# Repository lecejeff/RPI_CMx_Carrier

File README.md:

## SPONSOR

This project is proudly sponsored by [NextPCB](https://www.nextpcb.com). They have provided, free of charge, 2x assembled PCBA.

If you’re planning to build your own PCB, [NextPCB](https://www.nextpcb.com) offers reliable PCB fabrication and assembly services with fast turnaround times and competitive pricing, making it easier to bring your electronics projects from idea to reality.

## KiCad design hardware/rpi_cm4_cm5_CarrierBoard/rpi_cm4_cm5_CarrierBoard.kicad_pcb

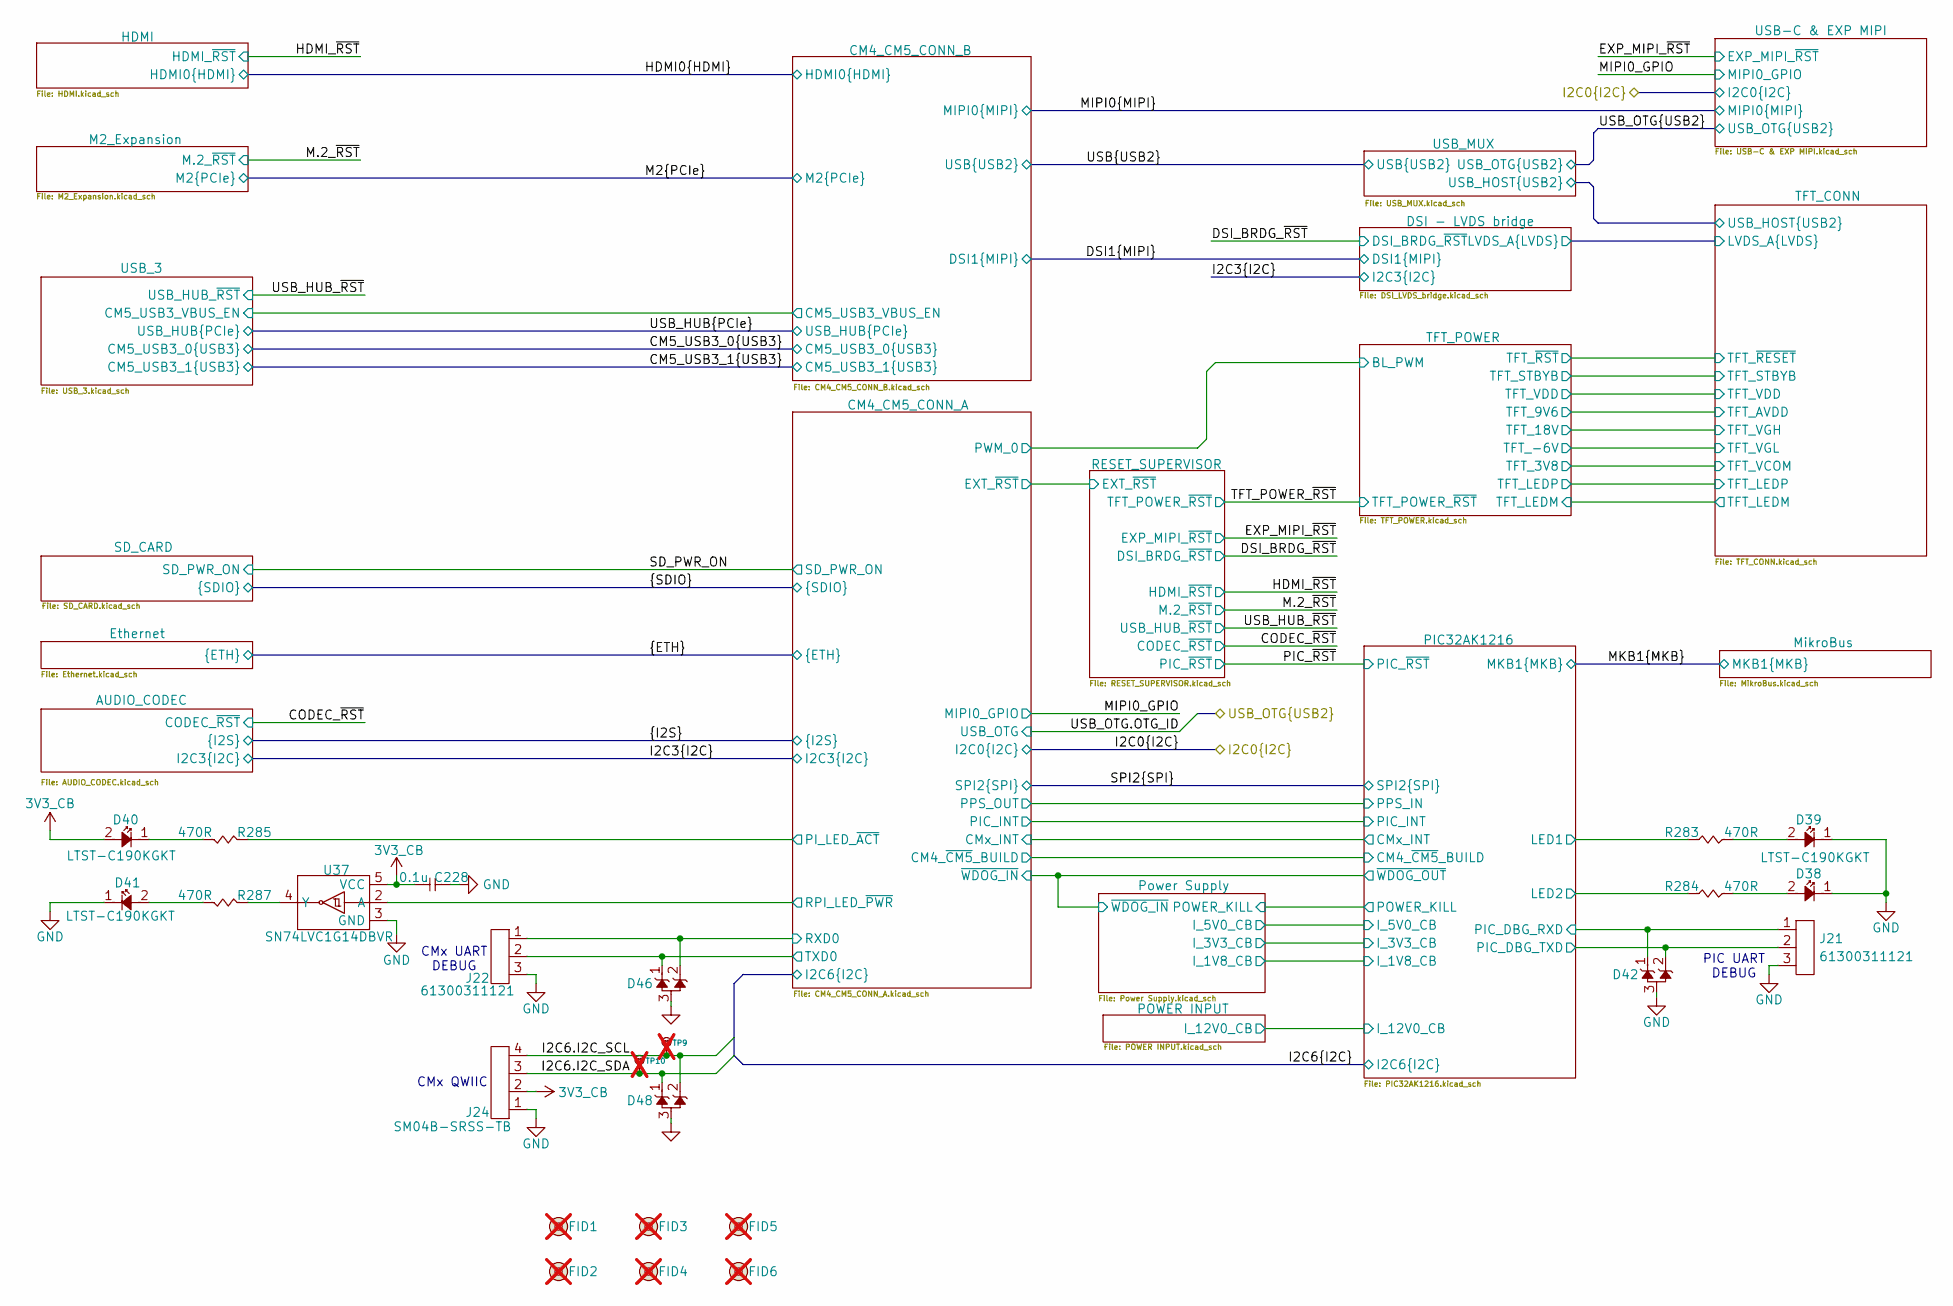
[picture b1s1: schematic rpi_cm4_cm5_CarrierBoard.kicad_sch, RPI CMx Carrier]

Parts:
C228: 0.1u; CAP_NONPOL_0402; Tolerance ±10%; Voltage Rating 50V; Manufacturer Part Number GRM155R71H104KE14D
D38, D39, D40, D41: LTST-C190KGKT; LED_0603; Tolerance NA; Manufacturer Part Number LTST-C190KGKT
D42, D46, D48: D1213A-02SOL-7; SOT-23-3; Manufacturer Part Number D1213A-02SOL-7
FID1, FID2, FID3, FID4, FID5, FID6: FIDUCIAL; not fitted
J21, J22: 61300311121; HEADER_3P_2_54MM; Current Rating 3A; Voltage Rating 250V; Manufacturer Part Number 61300311121
J24: SM04B-SRSS-TB; Current Rating 1A; Voltage Rating 50V; Manufacturer Part Number SM04B-SRSS-TB
R283, R284, R285, R287: 470R; RES_0402; Tolerance 1%; Manufacturer Part Number RC0402FR-07470RL
TP9, TP10: 28 mils; SMT_TP_28_MILS; Manufacturer Part Number NA; not fitted
U37: SN74LVC1G14DBVR; SOT-23-5; Supply Voltage 1.65V ~ 5.5V; Manufacturer Part Number SN74LVC1G14DBVR

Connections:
3V3_CB: C228.2, D40.2 (A), J24.2, U37.5 (VCC); also elsewhere on the board
/CM4_CM5_CONN_A/PI_LED_~ACT: R285.1; also elsewhere on the board
/CM4_CM5_CONN_A/RPI_LED_~PWR: U37.2 (A); also elsewhere on the board
/CM4_CM5_CONN_A/RXD0: D46.2 (A), J22.1; also elsewhere on the board
/CM4_CM5_CONN_A/TXD0: D46.1, J22.2; also elsewhere on the board
/I2C6.I2C_SCL: D48.2 (A), J24.4, TP9.1; also elsewhere on the board
/I2C6.I2C_SDA: D48.1, J24.3, TP10.1; also elsewhere on the board
/PIC32AK1216/LED1: R283.1; also elsewhere on the board
/PIC32AK1216/LED2: R284.1; also elsewhere on the board
/PIC32AK1216/PIC_DBG_RXD: D42.1, J21.1; also elsewhere on the board
/PIC32AK1216/PIC_DBG_TXD: D42.2 (A), J21.2; also elsewhere on the board
GND: C228.1, D38.1 (K), D39.1 (K), D41.1 (K), D42.3 (GND), D46.3 (GND), D48.3 (GND), J21.3, J22.3, J24.1, U37.3 (GND); also elsewhere on the board
unnamed: D38.2 (A), R284.2
unnamed: D39.2 (A), R283.2
unnamed: D40.1 (K), R285.2
unnamed: D41.2 (A), R287.2
unnamed: R287.1, U37.4 (Y)

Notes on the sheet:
CMx QWIIC
PIC UART DEBUG
CMx UART DEBUG

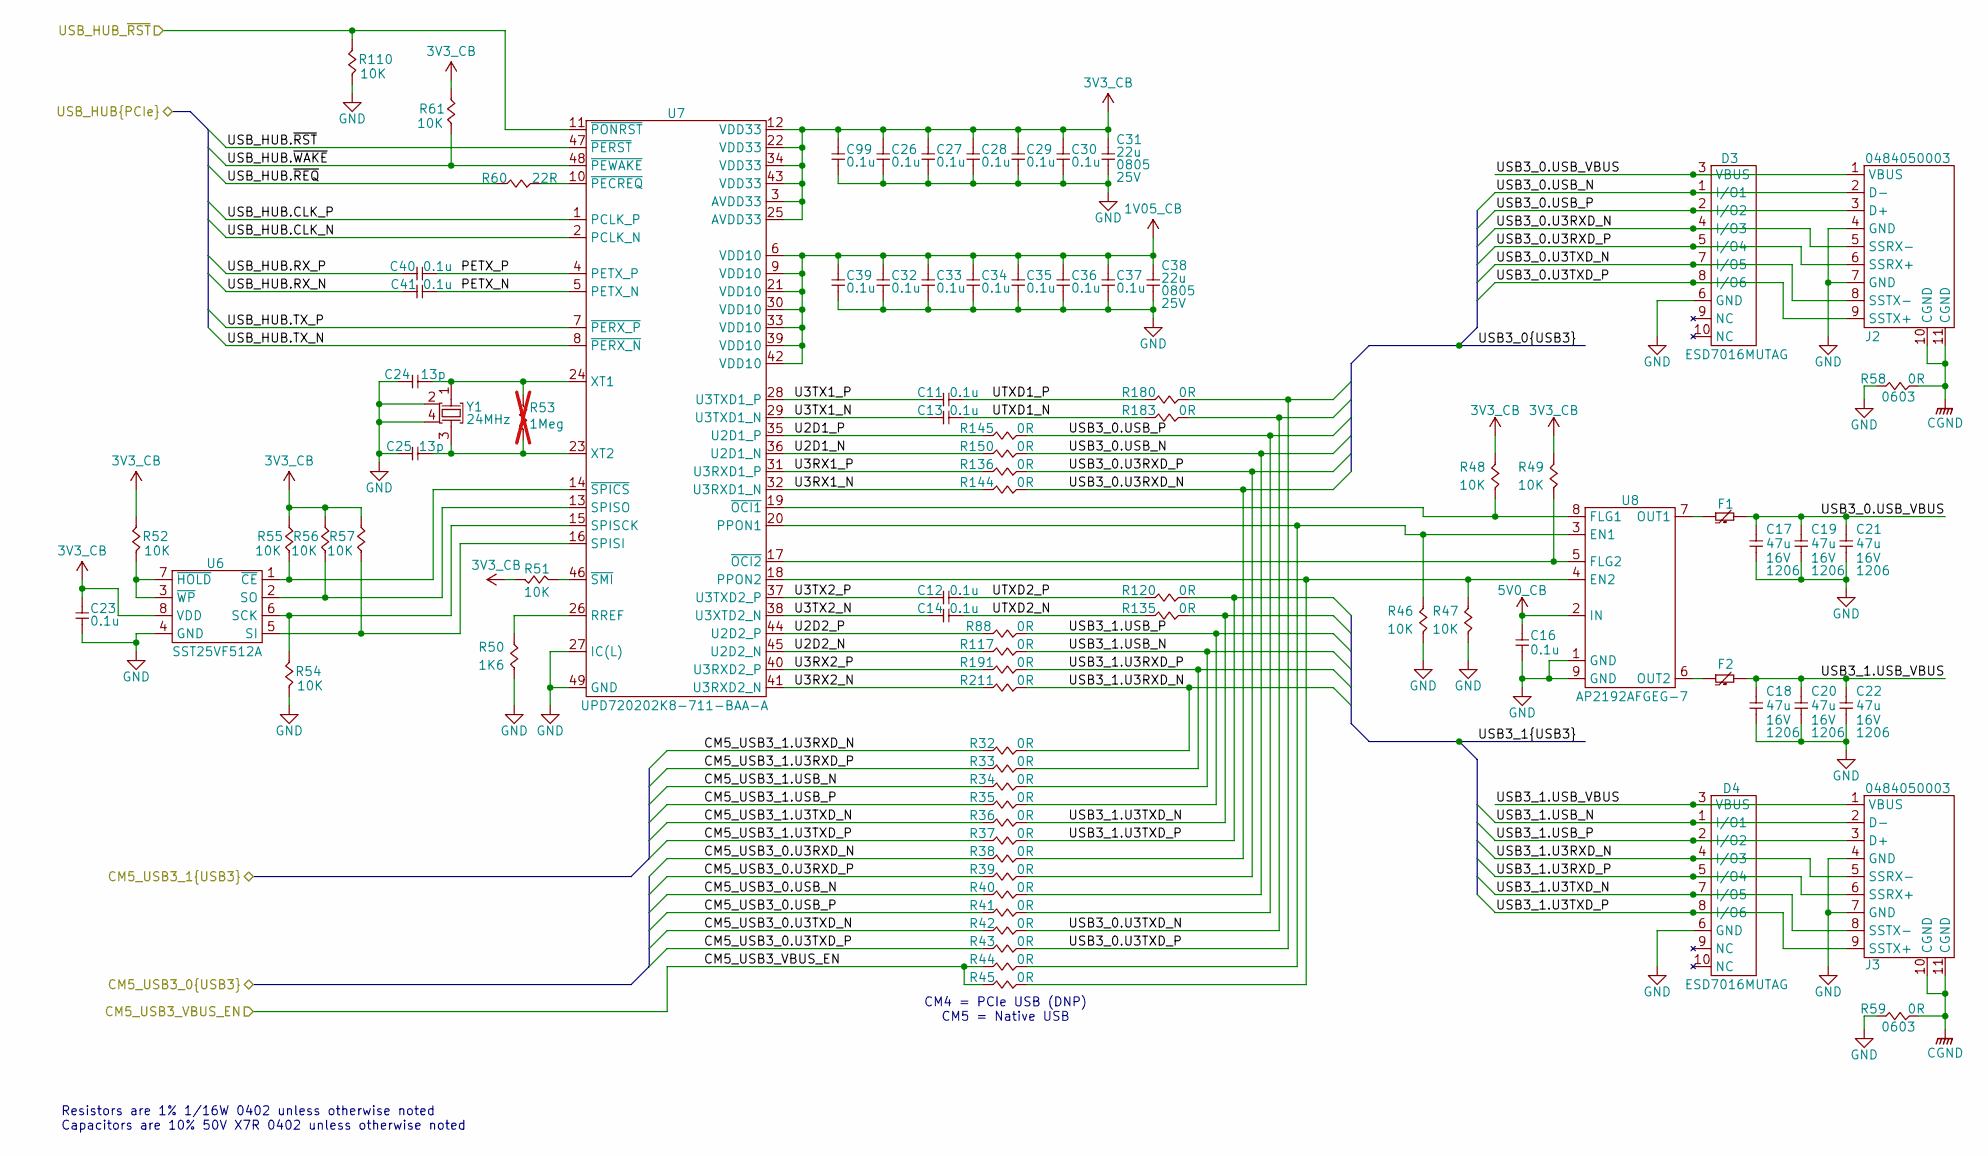
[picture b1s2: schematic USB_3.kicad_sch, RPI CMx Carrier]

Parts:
C11, C12, C13, C14, C16, C23, C26, C27, C28, C29, C30, C32, C33, C34, C35, C36, C37, C39, C40, C41, C99: 0.1u; CAP_NONPOL_0402; Tolerance ±10%; Voltage Rating 50V; Manufacturer Part Number GRM155R71H104KE14D
C17, C18, C19, C20, C21, C22: 47u; CAP_NONPOL_1206; Tolerance ±20%; Voltage Rating 16V; Manufacturer Part Number C3216X5R1C476M160AB
C24, C25: 13p; CAP_NONPOL_0402; Tolerance ±2%; Voltage Rating 50V; Manufacturer Part Number GJM1555C1H130GB01D
C31, C38: 22u; CAP_NONPOL_0805; Tolerance ±20%; Voltage Rating 25V; Manufacturer Part Number CL21A226MAYNNNE
D3, D4: ESD7016MUTAG; UDFN8; Manufacturer Part Number ESD7016MUTAG
F1, F2: MINISMDC050F-2; PTC_1812; Voltage 24V; Manufacturer Part Number MINISMDC050F-2
J2, J3: 0484050003; Current Rating 1.8A; Voltage Rating 30V; Manufacturer Part Number 0484050003
R32, R33, R34, R35, R36, R37, R38, R39, R40, R41, R42, R43, R44, R45, R88, R117, R120, R135, R136, R144, R145, R150, R180, R183, R191, R211: 0R; RES_0402; Tolerance 1%; Manufacturer Part Number RC0402FR-071KL
R46, R47, R48, R49, R51, R52, R54, R55, R56, R57, R61, R110: 10K; RES_0402; Tolerance 1%; Manufacturer Part Number RC0402FR-0710KL
R50: 1K6; RES_0402; Tolerance 1%; Manufacturer Part Number RC0402FR-131K6L
R53: 1Meg; RES_0402; Tolerance 1%; Manufacturer Part Number RC0402FR-131ML; not fitted
R58, R59: 0R; RES_0603; Tolerance 1%; Manufacturer Part Number RC0603JR-070RL
R60: 22R; RES_0402; Tolerance 1%; Manufacturer Part Number RC0402FR-0722RL
U6: SST25VF512A; SOIC-8-150mil; Supply Voltage 2.7V ~ 3.6V; Manufacturer Part Number SST25VF512A-33-4I-SAE
U7: UPD720202K8-711-BAA-A; 48-VFQFN-EP; Supply Voltage 1.05V ~ 3.3V; Manufacturer Part Number UPD720202K8-711-BAA-A
U8: AP2192AFGEG-7; U-DFN3030-8; Load Voltage 2.7V ~ 5.5V; Manufacturer Part Number AP2192AFGEG-7
Y1: 24MHz; 4-SMD_2mmx1_6mm; Tolerance ±20ppm; Manufacturer Part Number ABM11-24.000MHZ-D2X-T3

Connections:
1V05_CB: C32.2, C33.2, C34.2, C35.2, C36.2, C37.2, C38.2, C39.2, U7.6 (VDD10), U7.9 (VDD10), U7.21 (VDD10), U7.30 (VDD10), U7.33 (VDD10), U7.39 (VDD10), U7.42 (VDD10); also elsewhere on the board
3V3_CB: C23.2, C26.2, C27.2, C28.2, C29.2, C30.2, C31.2, C99.2, R48.2, R49.2, R51.2, R52.1, R55.1, R56.1, R57.1, R61.1, U6.8 (VDD), U7.3 (AVDD33), U7.12 (VDD33), U7.22 (VDD33), U7.25 (AVDD33), U7.34 (VDD33), U7.43 (VDD33); also elsewhere on the board
5V0_CB: C16.2, U8.2 (IN); also elsewhere on the board
/CM5_USB3_0.U3RXD_N: R38.1; also elsewhere on the board
/CM5_USB3_0.U3RXD_P: R39.1; also elsewhere on the board
/CM5_USB3_0.U3TXD_N: R42.1; also elsewhere on the board
/CM5_USB3_0.U3TXD_P: R43.1; also elsewhere on the board
/CM5_USB3_0.USB_N: R40.1; also elsewhere on the board
/CM5_USB3_0.USB_P: R41.1; also elsewhere on the board
/CM5_USB3_1.U3RXD_N: R32.1; also elsewhere on the board
/CM5_USB3_1.U3RXD_P: R33.1; also elsewhere on the board
/CM5_USB3_1.U3TXD_N: R36.1; also elsewhere on the board
/CM5_USB3_1.U3TXD_P: R37.1; also elsewhere on the board
/CM5_USB3_1.USB_N: R34.1; also elsewhere on the board
/CM5_USB3_1.USB_P: R35.1; also elsewhere on the board
/USB_3/CM5_USB3_VBUS_EN: R44.1, R45.1; also elsewhere on the board
/USB_3/PETX_N: C41.2, U7.5 (PETX_N)
/USB_3/PETX_P: C40.2, U7.4 (PETX_P)
/USB_3/U2D1_N: R150.1, U7.36 (U2D1_N)
/USB_3/U2D1_P: R145.1, U7.35 (U2D1_P)
/USB_3/U2D2_N: R117.1, U7.45 (U2D2_N)
/USB_3/U2D2_P: R88.1, U7.44 (U2D2_P)
/USB_3/U3RX1_N: R144.1, U7.32 (U3RXD1_N)
/USB_3/U3RX1_P: R136.1, U7.31 (U3RXD1_P)
/USB_3/U3RX2_N: R211.1, U7.41 (U3RXD2_N)
/USB_3/U3RX2_P: R191.1, U7.40 (U3RXD2_P)
/USB_3/U3TX1_N: C13.1, U7.29 (U3TXD1_N)
/USB_3/U3TX1_P: C11.1, U7.28 (U3TXD1_P)
/USB_3/U3TX2_N: C14.1, U7.38 (U3XTD2_N)
/USB_3/U3TX2_P: C12.1, U7.37 (U3TXD2_P)
/USB_3/USB3_0.U3RXD_N: D3.4 (I/O3), J2.5 (SSRX-), R38.2, R144.2
/USB_3/USB3_0.U3RXD_P: D3.5 (I/O4), J2.6 (SSRX+), R39.2, R136.2
/USB_3/USB3_0.U3TXD_N: D3.7 (I/O5), J2.8 (SSTX-), R42.2, R183.2
/USB_3/USB3_0.U3TXD_P: D3.8 (I/O6), J2.9 (SSTX+), R43.2, R180.2
/USB_3/USB3_0.USB_N: D3.1 (I/O1), J2.2 (D-), R40.2, R150.2
/USB_3/USB3_0.USB_P: D3.2 (I/O2), J2.3 (D+), R41.2, R145.2
/USB_3/USB3_0.USB_VBUS: C17.2, C19.2, C21.2, D3.3 (VBUS), F1.2, J2.1 (VBUS)
/USB_3/USB3_1.U3RXD_N: D4.4 (I/O3), J3.5 (SSRX-), R32.2, R211.2
/USB_3/USB3_1.U3RXD_P: D4.5 (I/O4), J3.6 (SSRX+), R33.2, R191.2
/USB_3/USB3_1.U3TXD_N: D4.7 (I/O5), J3.8 (SSTX-), R36.2, R135.2
/USB_3/USB3_1.U3TXD_P: D4.8 (I/O6), J3.9 (SSTX+), R37.2, R120.2
/USB_3/USB3_1.USB_N: D4.1 (I/O1), J3.2 (D-), R34.2, R117.2
/USB_3/USB3_1.USB_P: D4.2 (I/O2), J3.3 (D+), R35.2, R88.2
/USB_3/USB3_1.USB_VBUS: C18.2, C20.2, C22.2, D4.3 (VBUS), F2.2, J3.1 (VBUS)
/USB_3/UTXD1_N: C13.2, R183.1
/USB_3/UTXD1_P: C11.2, R180.1
/USB_3/UTXD2_N: C14.2, R135.1
/USB_3/UTXD2_P: C12.2, R120.1
/USB_HUB.CLK_N: U7.2 (PCLK_N); also elsewhere on the board
/USB_HUB.CLK_P: U7.1 (PCLK_P); also elsewhere on the board
/USB_HUB.RX_N: C41.1; also elsewhere on the board
/USB_HUB.RX_P: C40.1; also elsewhere on the board
/USB_HUB.TX_N: U7.8 (~PERX_N); also elsewhere on the board
/USB_HUB.TX_P: U7.7 (~PERX_P); also elsewhere on the board
/USB_HUB.~REQ: R60.1; also elsewhere on the board
/USB_HUB.~RST: U7.47 (~PERST); also elsewhere on the board
/USB_HUB.~WAKE: R61.2, U7.48 (~PEWAKE); also elsewhere on the board
/USB_HUB_~RST: R110.1, U7.11 (~PONRST); also elsewhere on the board
CGND: J2.10 (CGND), J2.11 (CGND), J3.10 (CGND), J3.11 (CGND), R58.1, R59.1; also elsewhere on the board
GND: C16.1, C17.1, C18.1, C19.1, C20.1, C21.1, C22.1, C23.1, C24.1, C25.1, C26.1, C27.1, C28.1, C29.1, C30.1, C31.1, C32.1, C33.1, C34.1, C35.1, C36.1, C37.1, C38.1, C39.1, C99.1, D3.6 (GND), D4.6 (GND), J2.4 (GND), J2.7 (GND), J3.4 (GND), J3.7 (GND), R46.1, R47.1, R50.1, R54.2, R58.2, R59.2, R110.2, U6.4 (GND), U7.27 (IC(L)), U7.49 (GND), U8.1 (GND), U8.9 (GND), Y1.2 (GND), Y1.4 (GND); also elsewhere on the board
unnamed: R54.1, U6.6 (SCK), U7.15 (SPISCK)
unnamed: R57.2, U6.5 (SI), U7.16 (SPISI)
unnamed: R56.2, U6.2 (SO), U7.13 (SPISO)
unnamed: R55.2, U6.1 (~CE), U7.14 (~SPICS)
unnamed: R52.2, U6.3 (~WP), U6.7 (~HOLD)
unnamed: R44.2, R46.2, U7.20 (PPON1), U8.3 (EN1)
unnamed: R45.2, R47.2, U7.18 (PPON2), U8.4 (EN2)
unnamed: R50.2, U7.26 (RREF)
unnamed: C24.2, R53.2, U7.24 (XT1), Y1.1 (XI)
unnamed: C25.2, R53.1, U7.23 (XT2), Y1.3 (XO)
unnamed: R48.1, U7.19 (~OCI1), U8.8 (FLG1)
unnamed: R49.1, U7.17 (~OCI2), U8.5 (FLG2)
unnamed: R60.2, U7.10 (~PECREQ)
unnamed: R51.1, U7.46 (~SMI)
unnamed: F1.1, U8.7 (OUT1)
unnamed: F2.1, U8.6 (OUT2)

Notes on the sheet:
CM4 = PCIe USB (DNP) CM5 = Native USB
Resistors are 1% 1/16W 0402 unless otherwise noted Capacitors are 10% 50V X7R 0402 unless otherwise noted

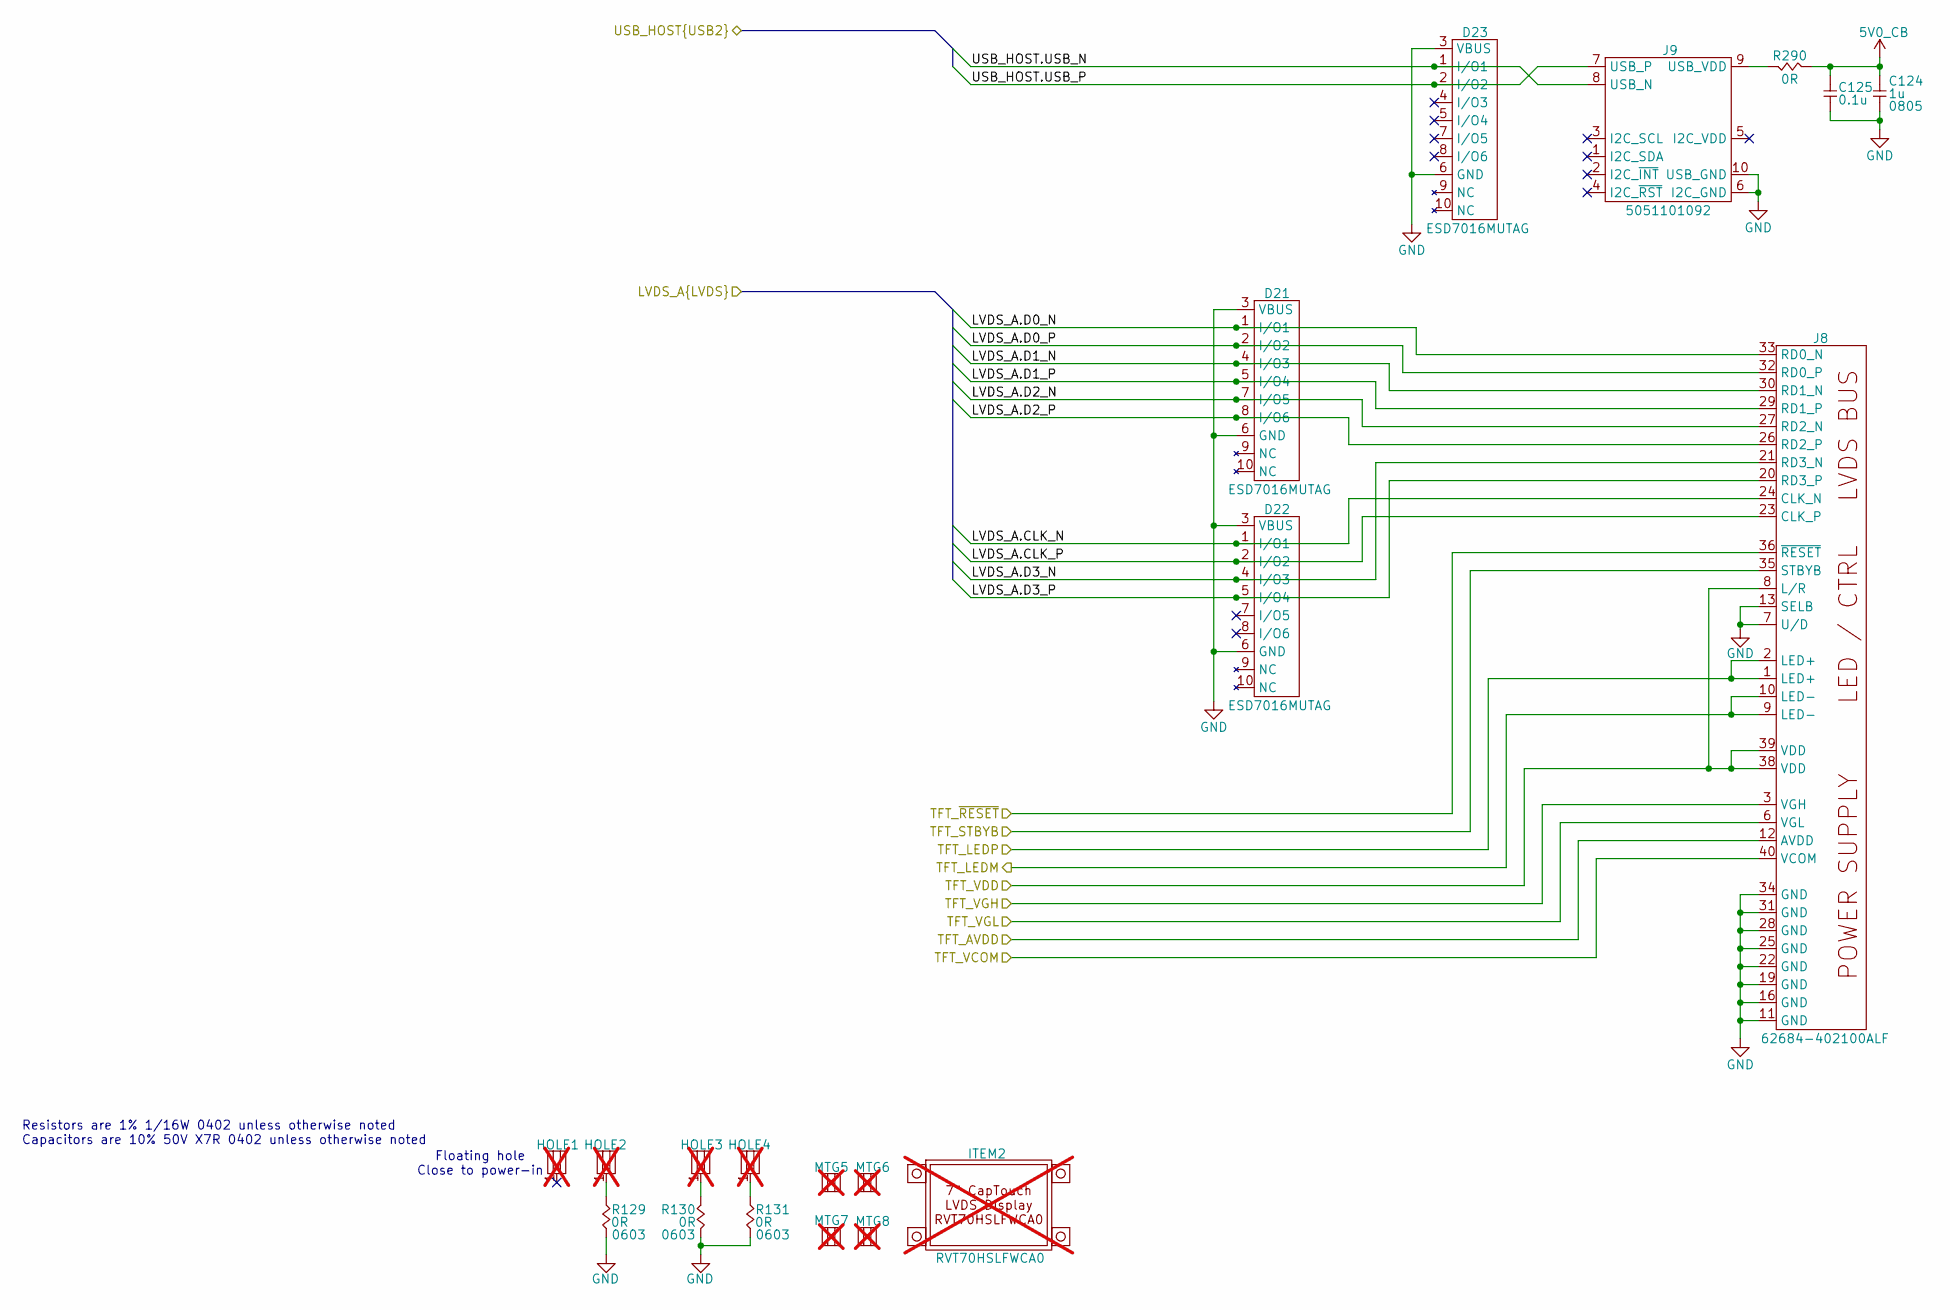
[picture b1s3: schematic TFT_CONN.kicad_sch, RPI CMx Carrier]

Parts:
C124: 1u; CAP_NONPOL_0805; Tolerance ±10%; Voltage Rating 50V; Manufacturer Part Number CC0805KKX7R9BB105
C125: 0.1u; CAP_NONPOL_0402; Tolerance ±10%; Voltage Rating 50V; Manufacturer Part Number GRM155R71H104KE14D
D21, D22, D23: ESD7016MUTAG; UDFN8; Manufacturer Part Number ESD7016MUTAG
HOLE1, HOLE2, HOLE3, HOLE4: MTG_hole_cir_5mm_pad_3mm_drill; not fitted
ITEM2: RVT70HSLFWCA0; Manufacturer Part Number SM-RVT70HSLFWCA0; not fitted
J8: 62684-402100ALF; Current Rating 0.5A; Voltage Rating 50V; Manufacturer Part Number 62684-402100ALF
J9: 5051101092; Current Rating 0.5A; Voltage Rating 50V; Manufacturer Part Number 5051101092
MTG5, MTG6, MTG7, MTG8: M0504-25-AL-7; Manufacturer Part Number M0504-25-AL-7; not fitted
R129, R130, R131: 0R; RES_0603; Tolerance 1%; Manufacturer Part Number RC0603JR-070RL
R290: 0R; RES_0402; Tolerance 1%; Manufacturer Part Number RC0402FR-071KL

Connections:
5V0_CB: C124.2, C125.2, R290.1; also elsewhere on the board
/DSI - LVDS bridge/LVDS_A.CLK_N: D22.1 (I/O1), J8.24 (CLK_N); also elsewhere on the board
/DSI - LVDS bridge/LVDS_A.CLK_P: D22.2 (I/O2), J8.23 (CLK_P); also elsewhere on the board
/DSI - LVDS bridge/LVDS_A.D0_N: D21.1 (I/O1), J8.33 (RD0_N); also elsewhere on the board
/DSI - LVDS bridge/LVDS_A.D0_P: D21.2 (I/O2), J8.32 (RD0_P); also elsewhere on the board
/DSI - LVDS bridge/LVDS_A.D1_N: D21.4 (I/O3), J8.30 (RD1_N); also elsewhere on the board
/DSI - LVDS bridge/LVDS_A.D1_P: D21.5 (I/O4), J8.29 (RD1_P); also elsewhere on the board
/DSI - LVDS bridge/LVDS_A.D2_N: D21.7 (I/O5), J8.27 (RD2_N); also elsewhere on the board
/DSI - LVDS bridge/LVDS_A.D2_P: D21.8 (I/O6), J8.26 (RD2_P); also elsewhere on the board
/DSI - LVDS bridge/LVDS_A.D3_N: D22.4 (I/O3), J8.21 (RD3_N); also elsewhere on the board
/DSI - LVDS bridge/LVDS_A.D3_P: D22.5 (I/O4), J8.20 (RD3_P); also elsewhere on the board
/TFT_CONN/TFT_LEDM: J8.9 (LED-), J8.10 (LED-); also elsewhere on the board
/TFT_CONN/TFT_LEDP: J8.1 (LED+), J8.2 (LED+); also elsewhere on the board
/TFT_CONN/TFT_VCOM: J8.40 (VCOM); also elsewhere on the board
/TFT_CONN/TFT_VDD: J8.8 (L/R), J8.38 (VDD), J8.39 (VDD); also elsewhere on the board
/TFT_CONN/TFT_VGH: J8.3 (VGH); also elsewhere on the board
/TFT_CONN/TFT_VGL: J8.6 (VGL); also elsewhere on the board
/TFT_CONN/USB_HOST.USB_N: D23.1 (I/O1), J9.8 (USB_N); also elsewhere on the board
/TFT_CONN/USB_HOST.USB_P: D23.2 (I/O2), J9.7 (USB_P); also elsewhere on the board
/TFT_POWER/TFT_9V6: J8.12 (AVDD); also elsewhere on the board
/TFT_POWER/TFT_~RST: J8.35 (STBYB), J8.36 (~RESET); also elsewhere on the board
GND: C124.1, C125.1, D21.3 (VBUS), D21.6 (GND), D22.3 (VBUS), D22.6 (GND), D23.3 (VBUS), D23.6 (GND), J8.7 (U/D), J8.11 (GND), J8.13 (SELB), J8.16 (GND), J8.19 (GND), J8.22 (GND), J8.25 (GND), J8.28 (GND), J8.31 (GND), J8.34 (GND), J9.6 (I2C_GND), J9.10 (USB_GND), R129.2, R130.2, R131.2; also elsewhere on the board
unnamed: HOLE2.1, R129.1
unnamed: HOLE3.1, R130.1
unnamed: HOLE4.1, R131.1
unnamed: J9.9 (USB_VDD), R290.2

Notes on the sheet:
Floating hole Close to power-in
Resistors are 1% 1/16W 0402 unless otherwise noted Capacitors are 10% 50V X7R 0402 unless otherwise noted

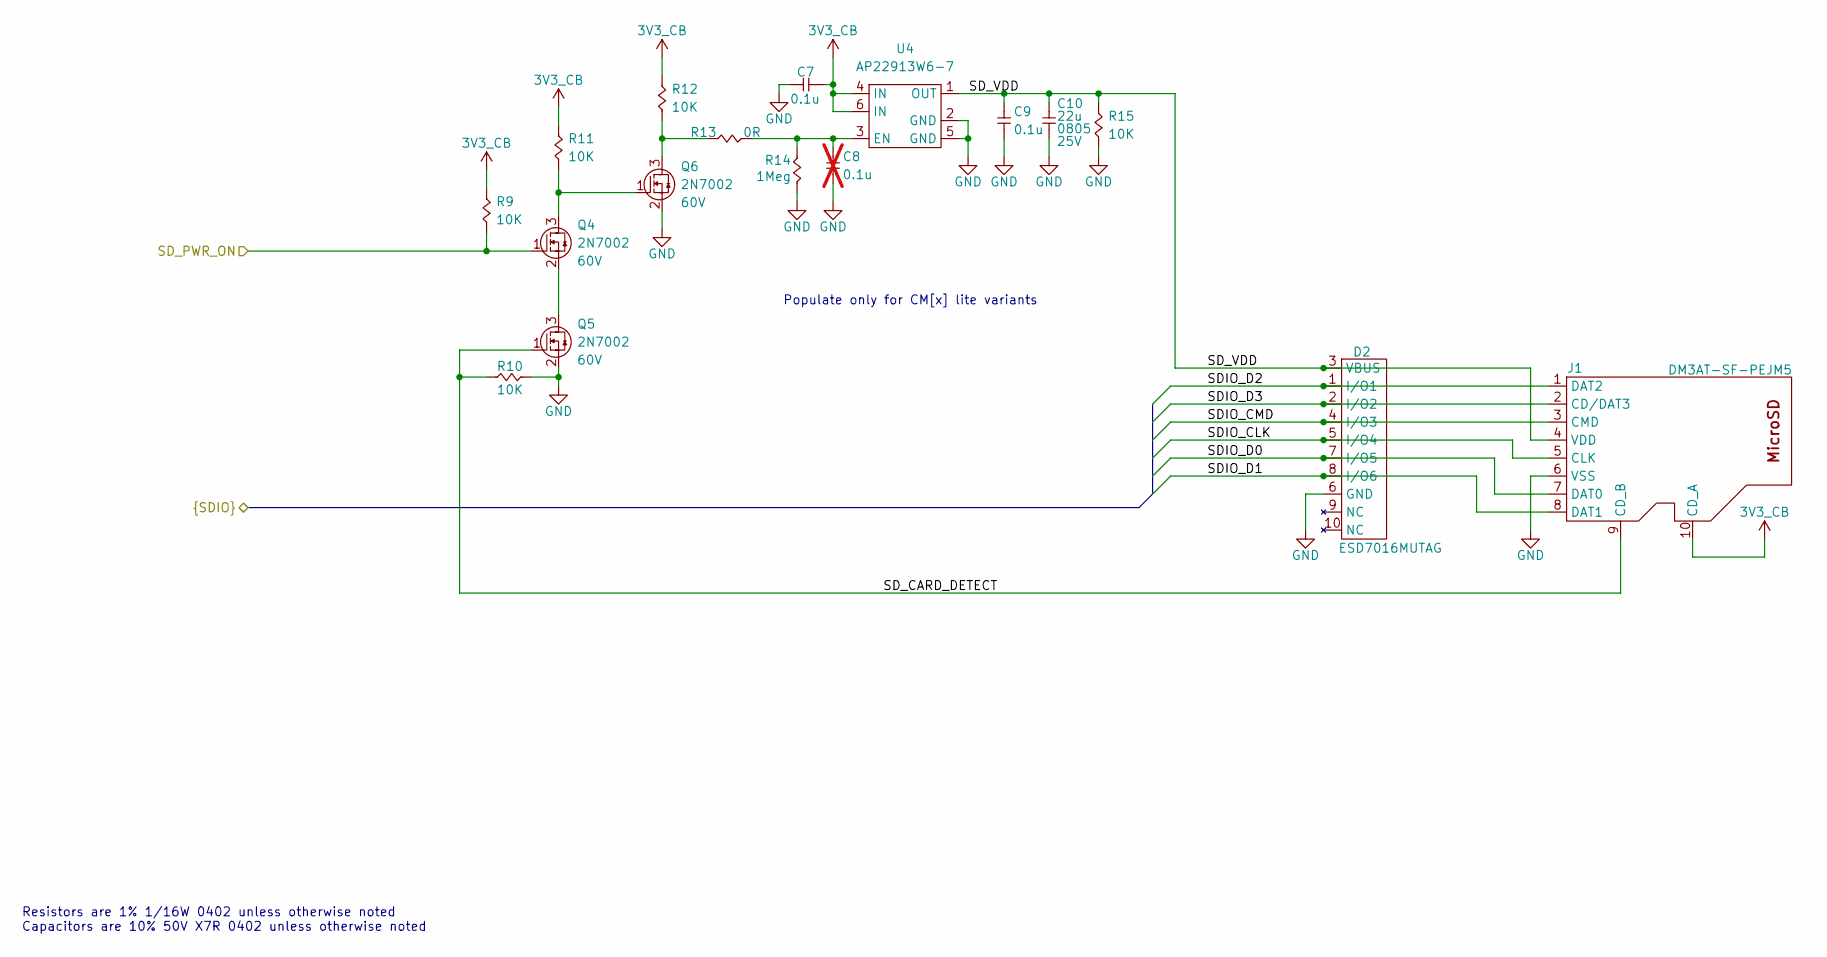
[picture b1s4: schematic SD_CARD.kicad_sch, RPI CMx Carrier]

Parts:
C7, C9: 0.1u; CAP_NONPOL_0402; Tolerance ±10%; Voltage Rating 50V; Manufacturer Part Number GRM155R71H104KE14D
C8: 0.1u; CAP_NONPOL_0402; Tolerance ±10%; Voltage Rating 50V; Manufacturer Part Number GRM155R71H104KE14D; not fitted
C10: 22u; CAP_NONPOL_0805; Tolerance ±20%; Voltage Rating 25V; Manufacturer Part Number CL21A226MAYNNNE
D2: ESD7016MUTAG; UDFN8; Manufacturer Part Number ESD7016MUTAG
J1: DM3AT-SF-PEJM5; Current Rating 0.5A; Voltage Rating 125V; Manufacturer Part Number DM3AT-SF-PEJM5
Q4, Q5, Q6: 2N7002; SOT-23-3; Manufacturer Part Number 2N7002-7-F
R9, R10, R11, R12, R15: 10K; RES_0402; Tolerance 1%; Manufacturer Part Number RC0402FR-0710KL
R13: 0R; RES_0402; Tolerance 1%; Manufacturer Part Number RC0402FR-071KL
R14: 1Meg; RES_0402; Tolerance 1%; Manufacturer Part Number RC0402FR-131ML
U4: AP22913W6-7; SOT-23-6; Load Voltage 1.5V ~ 5.5V; Manufacturer Part Number AP22913W6-7

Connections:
3V3_CB: C7.2, J1.10 (CD_A), R9.2, R11.2, R12.2, U4.4 (IN), U4.6 (IN); also elsewhere on the board
/SDIO_CLK: D2.5 (I/O4), J1.5 (CLK); also elsewhere on the board
/SDIO_CMD: D2.4 (I/O3), J1.3 (CMD); also elsewhere on the board
/SDIO_D0: D2.7 (I/O5), J1.7 (DAT0); also elsewhere on the board
/SDIO_D1: D2.8 (I/O6), J1.8 (DAT1); also elsewhere on the board
/SDIO_D2: D2.1 (I/O1), J1.1 (DAT2); also elsewhere on the board
/SDIO_D3: D2.2 (I/O2), J1.2 (CD/DAT3); also elsewhere on the board
/SD_CARD/SD_CARD_DETECT: J1.9 (CD_B), Q5.1 (G), R10.2
/SD_CARD/SD_VDD: C9.2, C10.2, D2.3 (VBUS), J1.4 (VDD), R15.2, U4.1 (OUT)
/SD_PWR_ON: Q4.1 (G), R9.1; also elsewhere on the board
GND: C7.1, C8.1, C9.1, C10.1, D2.6 (GND), J1.6 (VSS), Q5.2 (S), Q6.2 (S), R10.1, R14.1, R15.1, U4.2 (GND), U4.5 (GND); also elsewhere on the board
unnamed: Q4.3 (D), Q6.1 (G), R11.1
unnamed: Q4.2 (S), Q5.3 (D)
unnamed: Q6.3 (D), R12.1, R13.1
unnamed: C8.2, R13.2, R14.2, U4.3 (EN)

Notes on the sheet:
Populate only for CM[x] lite variants
Resistors are 1% 1/16W 0402 unless otherwise noted Capacitors are 10% 50V X7R 0402 unless otherwise noted
